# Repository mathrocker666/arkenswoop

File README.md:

# Arkenswoop

A WIP fork of [jimmerricks's Swoop](https://github.com/jimmerricks/swoop), which is a fork of [David Barr's Sweep](https://github.com/davidphilipbarr/Sweep), which is itself based on the fabulous [Ferris by Pierre Chevalier](https://github.com/pierrechevalier83/ferris).

| Wireless Arkenswoop v0.9.2, front | Wireless Arkenswoop v0.9.2, back |
| :---: | :---: |
|  |  |

### Features

⭕ Low profile Kailh Choc switches  
⭕ Hotswap  
⭕ Dual side-scrolling encoder  
⭕ Optional SSD1306 OLED or nice!view on each half\
⭕ Power switch for battery management  
⭕ Wireless split over Bluetooth with a nice!nano on each half\
⭕ Plate style case with mcu cover

### Components list

The wireless-only Arkenswoop v0.9.2 uses the following parts.

* 1× PCB Kit (1.6mm thickness when ordering)
* 1× back plate kit (optional, 1.2mm thickness when ordering)
* 2× nice!nano controllers, one per half
* 34× Kailh Choc v1 switches
* 34× Kailh Choc hotswap sockets (PG1350)
* 34× keycaps
* 34× SMD diodes (1N4148W, SOD-123)
* 2× side-scrolling encoders EVQWGD001
* Optional displays, one per half: 128×32 SSD1306 OLED, or nice!view with a 5-pin 2.54 mm socket and a 3.3 V nice!nano. See the [display assembly guide](BUILD_GUIDE.md#display).
* 2× MCU cover (optional, 1mm thickness when ordering)
* 2× reset switches (optional; B3U-1000P(M))
* Some little rubber feet/bumpers (minimum of 4 on each side)
* 2× MSK 12C02 power switches
* 2× LiPo batteries (301230 or 301228), one per half
* 1× USB data cable for flashing and charging

## Backplates

| Left | Right |
| :---: | :---: |
|  |  |

## Earlier wired builds

<details>
    <summary>Assembled Arkenswoop 0.6.0</summary>
    
</details>
<details>
    <summary>Back of assembled Arkenswoop 0.6.0</summary>
    
</details>

[Wired prototype assembly photos](images/build)

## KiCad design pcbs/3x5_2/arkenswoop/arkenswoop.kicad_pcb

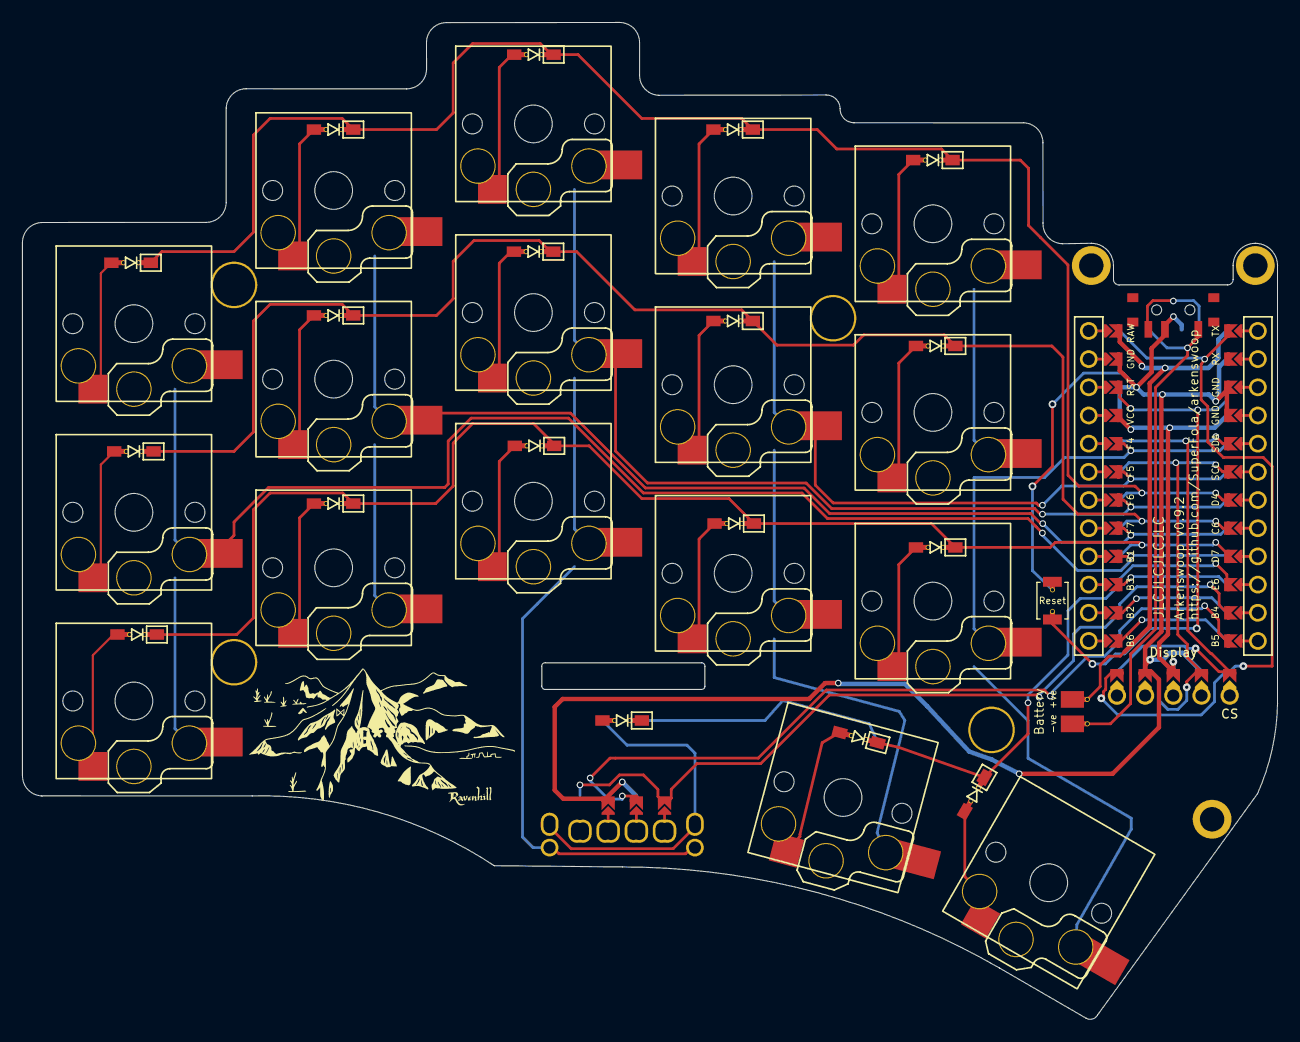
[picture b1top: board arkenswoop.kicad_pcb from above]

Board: 2 copper layers, 113.1 x 89.8 mm, 48 parts (0 on the bottom side), 22 nets.

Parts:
BT1: Battery; Battery_pads_reversible
D1, D2, D3, D4, D5, D6, D7, D8, D9, D10, D11, D12, D13, D14, D15, D16, D17: 1N4148W; D3_SMD
ED1: 1N4148W; D3_SMD
EN2: EVQWGD001; RollerEncoder
H1, H2, H3, H4: M2 Hole; M2_hole_4.2mm
O1: Display; Display_jumpers
PSW1: Power
RSW1: Reset
Ref**: Val**; M2_hole_3.5mm
Ref**#2, Ref**#3: Val**; M2_hole_3.5mm
SW1, SW2, SW3, SW4, SW5, SW6, SW7, SW8, SW9, SW10, SW11, SW12, SW13, SW14, SW15, SW16, SW17: Choc; Kailh-pg1350-socket-reversible
U1: ProMicro; ProMicro_jumpers

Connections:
GND: EN2.C, O1.4, PSW1.2 (B), RSW1.2, U1.3 (GND), U1.4 (GND), U1.23 (GND)
unnamed: D1.2 (A), SW1.2
unnamed: D6.2 (A), SW6.2
unnamed: D11.2 (A), SW11.2
VCC: O1.3, U1.21 (VCC)
col0: SW1.1, SW6.1, SW11.1, U1.16 (B1)
col1: SW2.1, SW7.1, SW12.1, U1.17 (F7)
col2: EN2.S1, SW3.1, SW8.1, SW13.1, U1.18 (F6)
col3: SW4.1, SW9.1, SW14.1, SW16.1, U1.19 (F5)
col4: SW5.1, SW10.1, SW15.1, SW17.1, U1.20 (F4)
display_cs: O1.5, U1.1 (TX)
eda: EN2.A, U1.11 (B4)
edb: EN2.B, U1.12 (B5)
er0: ED1.2 (A), EN2.S2
raw: BT1.1 (+), U1.24 (RAW)
reset: RSW1.1, U1.22 (RST)
row0: D1.1 (K), D2.1 (K), D3.1 (K), D4.1 (K), D5.1 (K), U1.7 (D4)
row1: D6.1 (K), D7.1 (K), D8.1 (K), D9.1 (K), D10.1 (K), U1.8 (C6)
row2: D11.1 (K), D12.1 (K), D13.1 (K), D14.1 (K), D15.1 (K), U1.9 (D7)
row3: D16.1 (K), D17.1 (K), ED1.1 (K), U1.10 (E6)
sda: O1.1, U1.5 (SDA)
sla: O1.2, U1.6 (SCL)
